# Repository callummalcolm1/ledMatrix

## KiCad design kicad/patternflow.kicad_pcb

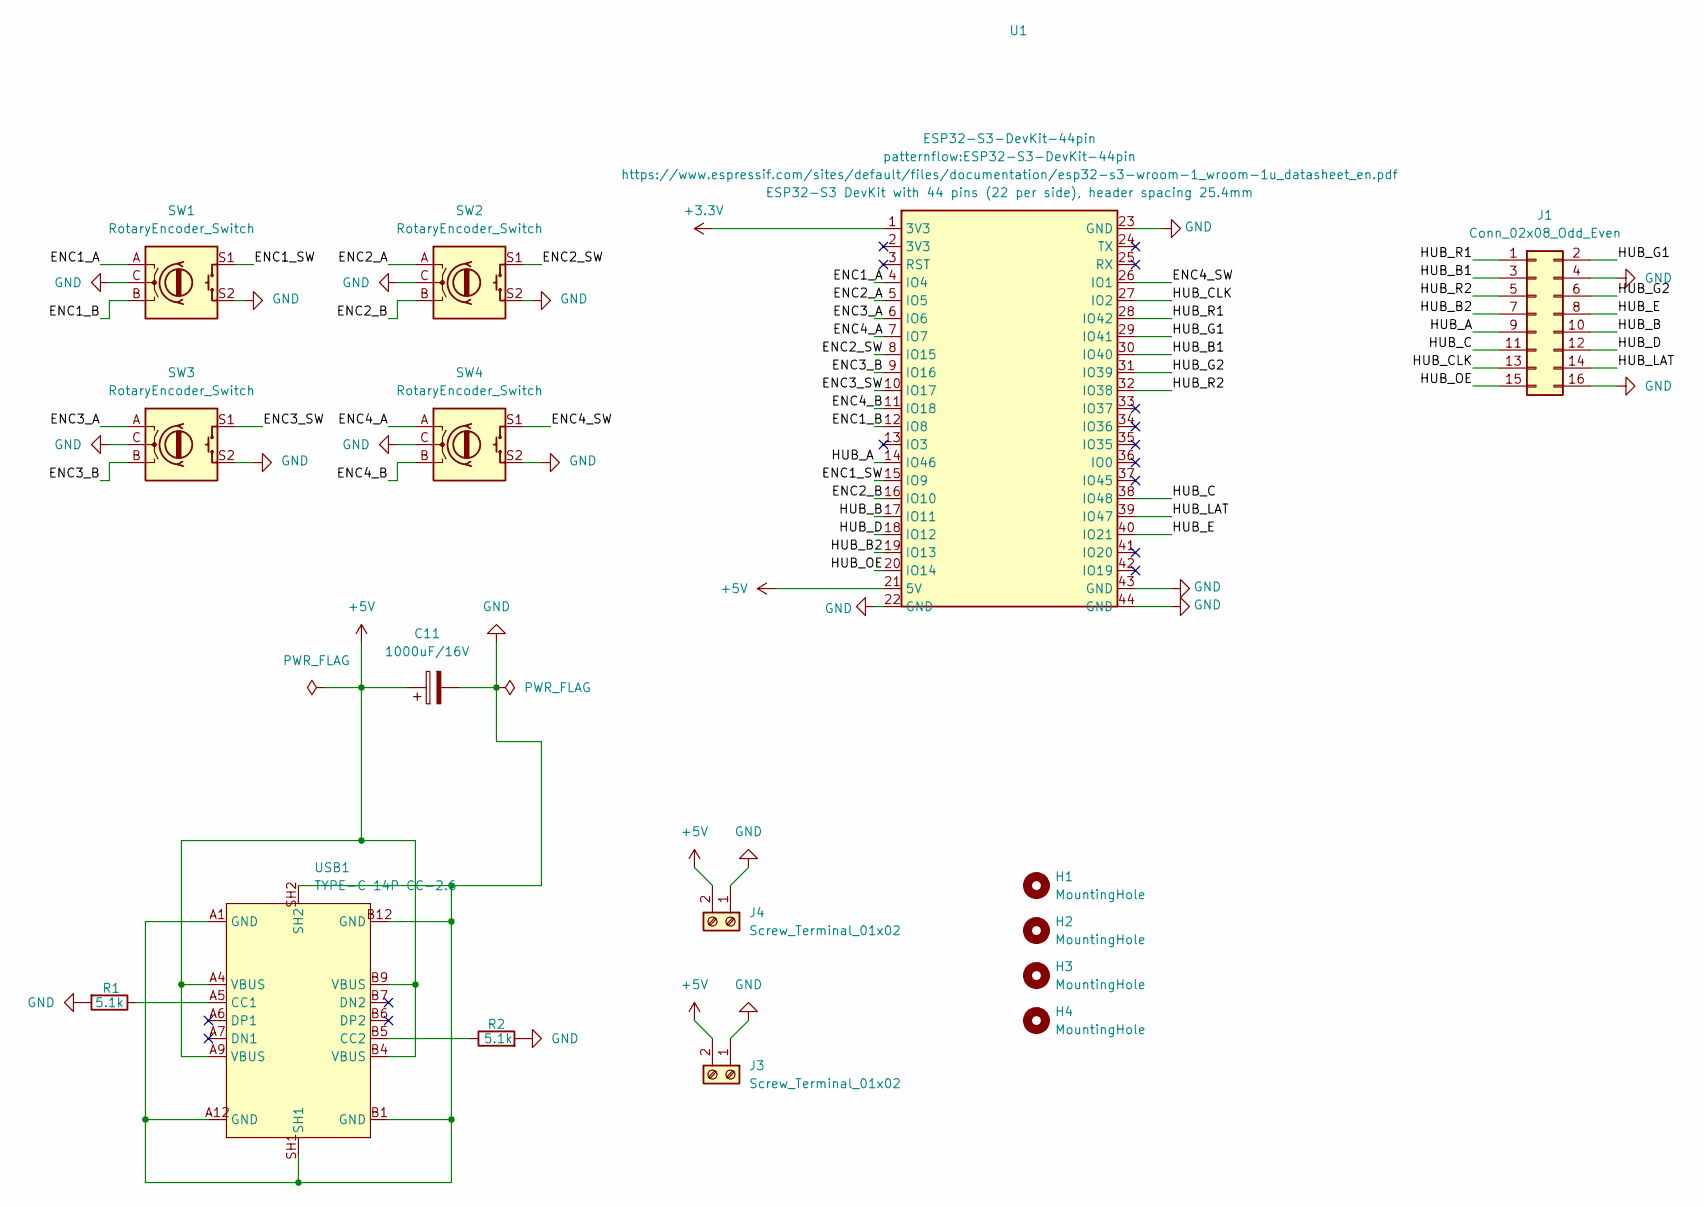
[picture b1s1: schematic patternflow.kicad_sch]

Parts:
C11: 1000uF/16V; CP_Radial_D10.0mm_P5.00mm
H1, H2, H3, H4: MountingHole; MountingHole_2.7mm_M2.5_ISO7380
J1: Conn_02x08_Odd_Even; PinHeader_2x08_P2.54mm_Vertical
J3, J4: Screw_Terminal_01x02; TerminalBlock_MaiXu_MX126-5.0-02P_1x02_P5.00mm
R1, R2: 5.1k; R_Axial_DIN0207_L6.3mm_D2.5mm_P7.62mm_Horizontal
SW1, SW2, SW3, SW4: RotaryEncoder_Switch; RotaryEncoder_Bourns_Vertical_PEC12R-3x17F-Sxxxx
U1: ESP32-S3-DevKit-44pin
USB1: TYPE-C 14P CC-2.6; TYPE-C-TH_TYPE-C-14P-CC-2.6; MPN TYPE-C 14P CC-2.6; LCSC Part C5187475

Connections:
+3.3V: U1.1 (3V3)
+5V: C11.1, J3.2, J4.2, U1.21 (5V), USB1.A4 (VBUS), USB1.A9 (VBUS), USB1.B4 (VBUS), USB1.B9 (VBUS)
/ENC1_A: SW1.A, U1.4 (IO4)
/ENC1_B: SW1.B, U1.12 (IO8)
/ENC1_SW: SW1.S1, U1.15 (IO9)
/ENC2_A: SW2.A, U1.5 (IO5)
/ENC2_B: SW2.B, U1.16 (IO10)
/ENC2_SW: SW2.S1, U1.8 (IO15)
/ENC3_A: SW3.A, U1.6 (IO6)
/ENC3_B: SW3.B, U1.9 (IO16)
/ENC3_SW: SW3.S1, U1.10 (IO17)
/ENC4_A: SW4.A, U1.7 (IO7)
/ENC4_B: SW4.B, U1.11 (IO18)
/ENC4_SW: SW4.S1, U1.26 (IO1)
/HUB_A: J1.9, U1.14 (IO46)
/HUB_B: J1.10, U1.17 (IO11)
/HUB_B1: J1.3, U1.30 (IO40)
/HUB_B2: J1.7, U1.19 (IO13)
/HUB_C: J1.11, U1.38 (IO48)
/HUB_CLK: J1.13, U1.27 (IO2)
/HUB_D: J1.12, U1.18 (IO12)
/HUB_E: J1.8, U1.40 (IO21)
/HUB_G1: J1.2, U1.29 (IO41)
/HUB_G2: J1.6, U1.31 (IO39)
/HUB_LAT: J1.14, U1.39 (IO47)
/HUB_OE: J1.15, U1.20 (IO14)
/HUB_R1: J1.1, U1.28 (IO42)
/HUB_R2: J1.5, U1.32 (IO38)
GND: C11.2, J1.4, J1.16, J3.1, J4.1, R1.2, R2.2, SW1.C, SW1.S2, SW2.C, SW2.S2, SW3.C, SW3.S2, SW4.C, SW4.S2, U1.22 (GND), U1.23 (GND), U1.43 (GND), U1.44 (GND), USB1.A1 (GND), USB1.A12 (GND), USB1.B1 (GND), USB1.B12 (GND), USB1.SH1, USB1.SH2
unnamed: R1.1, USB1.A5 (CC1)
unnamed: R2.1, USB1.B5 (CC2)

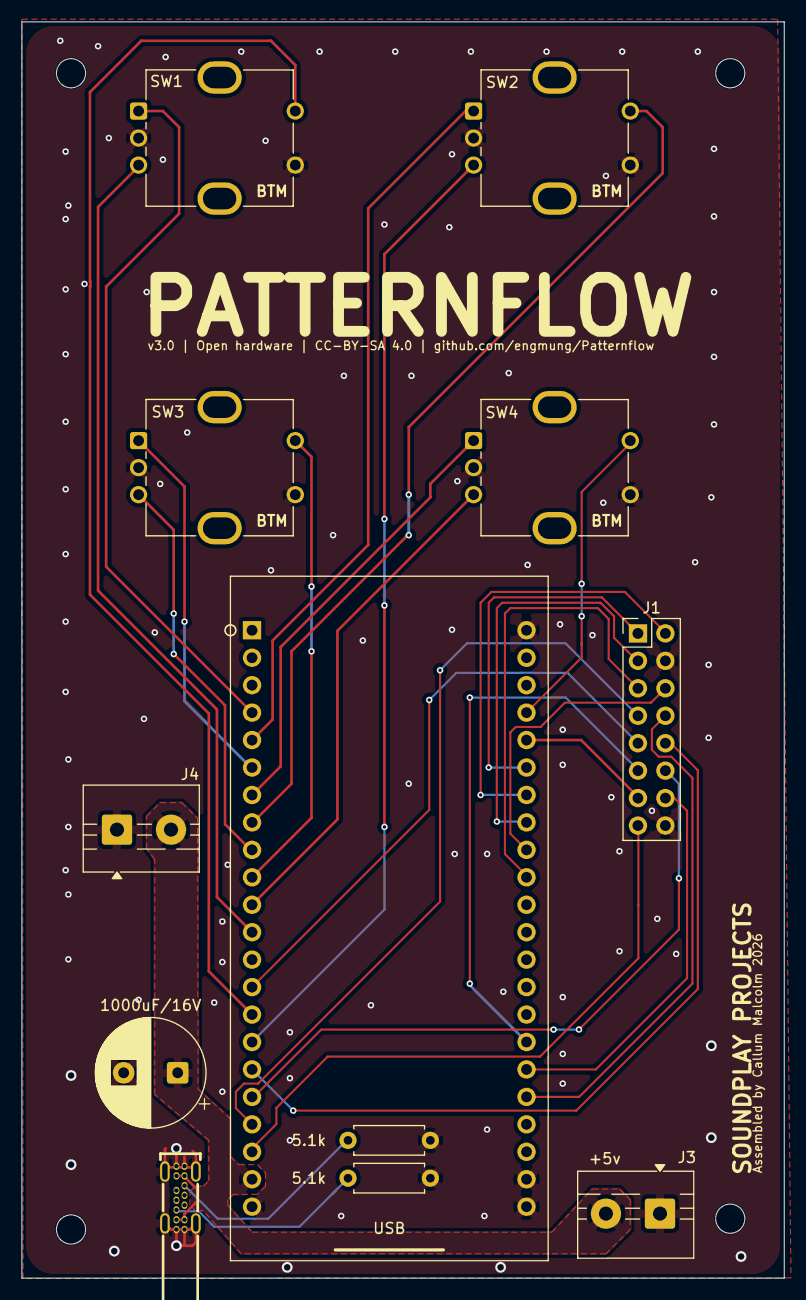
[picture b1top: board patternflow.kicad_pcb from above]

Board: 2 copper layers, 70.5 x 116.2 mm, 16 parts (0 on the bottom side), 30 nets.

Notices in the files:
kicad/patternflow.kicad_pcb:
v3.0 | Open hardware | CC-BY-SA 4.0 | github.com/engmung/Patternflow
